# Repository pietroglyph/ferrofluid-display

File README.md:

# ferrofluid-display
Firmware, animation, and control code for a electromagnet-powered ferrofluid display.

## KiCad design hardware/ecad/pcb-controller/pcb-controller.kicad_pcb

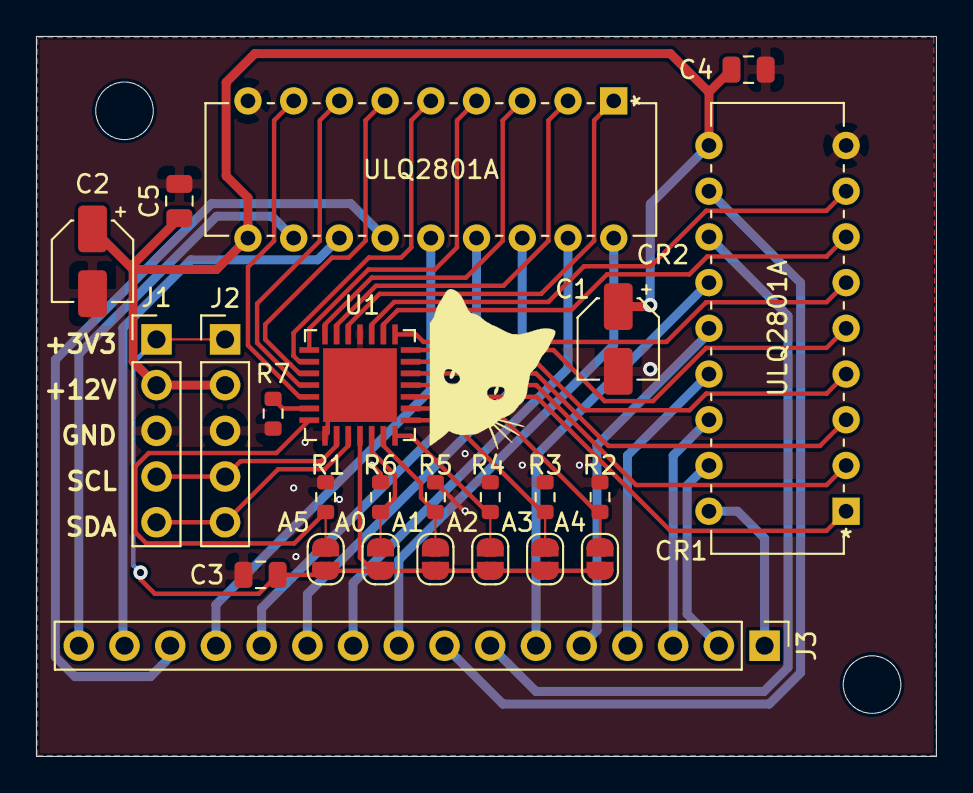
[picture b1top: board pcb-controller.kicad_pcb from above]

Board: 2 copper layers, 50.0 x 40.0 mm, 26 parts (0 on the bottom side), 44 nets.

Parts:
A0, A1, A2, A3, A4, A5: SolderJumper_2_Open; SolderJumper-2_P1.3mm_Open_RoundedPad1.0x1.5mm
C1, C2: CP1; CP_Elec_4x5.4
C3, C4, C5: 0.1 uF; C_0805_2012Metric
CR1, CR2: ULQ2801A
H1, H2: MountingHole; MountingHole_3.2mm_M3
J1, J2: Conn_01x05; PinHeader_1x05_P2.54mm_Vertical
J3: Conn_01x16; PinHeader_1x16_P2.54mm_Vertical
R1, R2, R3, R4, R5, R6, R7: 10k; R_0603_1608Metric
U1: PCA9685BS; QFN65P600X600X100-29N

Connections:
+3V3: A0.1, A1.1, A2.1, A3.1, A4.1, A5.1, C3.1, J1.1, J2.1, U1.25
+12V: C1.1, C2.1, C4.1, C5.1, CR1.10, CR2.10, J1.2, J2.2
/A0: A0.2, R6.1, U1.26
/A1: A1.2, R5.1, U1.27
/A2: A2.2, R4.1, U1.28
/A3: A3.2, R3.1, U1.1
/A4: A4.2, R2.1, U1.2
/A5: A5.2, R1.1, U1.21
GND: C1.2, C2.2, C3.2, C4.2, C5.2, CR1.9, CR2.9, J1.3, J2.3, R1.2, R2.2, R3.2, R4.2, R5.2, R6.2, R7.2, U1.11, U1.22, U1.29
unnamed: CR1.1, U1.3
unnamed: CR1.2, U1.4
unnamed: CR1.3, U1.5
unnamed: CR1.4, U1.6
unnamed: CR1.5, U1.7
unnamed: CR1.6, U1.8
unnamed: CR1.7, U1.9
unnamed: CR1.8, U1.10
unnamed: CR1.11, J3.8
unnamed: CR1.12, J3.7
unnamed: CR1.13, J3.6
unnamed: CR1.14, J3.5
unnamed: CR1.15, J3.4
unnamed: CR1.16, J3.3
unnamed: CR1.17, J3.2
unnamed: CR1.18, J3.1
unnamed: CR2.1, U1.12
unnamed: CR2.2, U1.13
unnamed: CR2.3, U1.14
unnamed: CR2.4, U1.15
unnamed: CR2.5, U1.16
unnamed: CR2.6, U1.17
unnamed: CR2.7, U1.18
unnamed: CR2.8, U1.19
unnamed: CR2.11, J3.16
unnamed: CR2.12, J3.15
unnamed: CR2.13, J3.14
unnamed: CR2.14, J3.13
unnamed: CR2.15, J3.12
unnamed: CR2.16, J3.11
unnamed: CR2.17, J3.10
unnamed: CR2.18, J3.9
unnamed: J1.4, J2.4, U1.23
unnamed: J1.5, J2.5, U1.24
unnamed: R7.1, U1.20

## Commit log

2021-10-31 Update .gitignore to exclude some CMake files
2021-10-31 Add basic project outline
2021-11-04 Set up a compile_commands.json and gitignore for clangd
2021-11-04 Add thresholding- and edge-detection-based display corner detection
2021-11-06 Add hardware directory structure and pcb coil v1
2021-11-06 Add mcad folder
2021-11-07 Add initial work on animation code
2021-11-07 Remove unused options from tracking CMakeLists
2021-11-07 Add initial version of website, with theme and GH action
2021-11-07 deploy: 8cd447ee73312b138034860ab5582cf2dd577925
2021-11-08 Added controller design files. Need to add addresses.
2021-11-08 Added I2C headers and finished PCA9685 schematic wires.
2021-11-08 Fill out website a little bit more
2021-11-08 deploy: efb6bf612e4b9bd919eba291d5f942247d1d5515
2021-11-14 Finished Rev 1 of controller pcb.
2021-11-14 deploy: c7c88280d730185e005096958d3cd155b8f524eb
2021-11-15 Switched to 16 pin header from 32 pin connector. Updated gerber.
2021-11-15 deploy: abc7ec6a708017383b983a7d375b9358067f2693
2021-11-18 Fix visual backend and add test images
2021-11-18 deploy: 252b31852fd4b8733a5ba26198d3494dfbf380dd
2021-11-19 Fixed symbol libraries.
2021-11-24 Added subsystems pages. Put requirements on journey page.
2021-11-24 deploy: 68dbbda1008af753ef7e3fd47abec90abaeec651
2021-12-02 Add simple file backend
2021-12-02 Fix bugs with file backend
2021-12-03 Added Arduino firmware for turning magnets on/off based on coordinate
2021-12-05 Added support for connecting to multiple PCA ICs
2021-12-10 Add better test animation
2021-12-10 Format code and improve handling of different max duty cycles
2021-12-10 Make firmware read from SD and do interpolation and use modern C++
2021-12-10 deploy: c3130c0771fd627b3073a5a7c611cfc3ed057908
2021-12-10 Use correct max duty cycle instead of uint16 maximum
2021-12-10 deploy: 2b08edafac9fc4fc9de33876016798d200687e86
2021-12-11 Added budget.
2021-12-11 Fix serial command parsing and add off command
2021-12-12 Add avr_stl so that we compile for AVR-based Arduinos
2021-12-12 deploy: 1ccc70c4ad434bdfe2e2123518465e2a0fa372df
2021-12-12 Add initial systems page.
2021-12-12 deploy: 3b321c5df0429ae49f3630088eeb76660fbda2ed
2021-12-12 Add shortcodes for page navigation arrows
2021-12-12 Oops forgot to format some animation code
2021-12-12 Pull submodule
2021-12-12 Added content to tank section.
2021-12-12 Create journey page structure
2021-12-12 deploy: a01d33379276a89cc5a79bd3d5627d702e178bca
2021-12-12 Added images to systems.md.
2021-12-12 deploy: eca00d64d520b0ca711811684c26ca2ad0611d8d
2021-12-12 Added Content to Magnets
2021-12-12 deploy: d716388dbbb42d940d0c2795224ccd17d996e76b
2021-12-12 Nuke .gitmodules
2021-12-12 Re-add submodule
2021-12-12 Add serial reading option on mcu and serial writing
2021-12-12 Added Image
2021-12-12 deploy: 4070a99a33f397c962793e3b17ff82bc78767587
2021-12-12 Added SPI sd-card reading for Arduinos
2021-12-13 Add serial backend and serial mode on the MCU
2021-12-13 Add build instructions
2021-12-13 deploy: edf58630346c6725c5c925d4f606dcfe03218655
2021-12-13 deploy: ba1b45fbebad2c7f0c8d01066d3f39bcef6cab83
2021-12-13 deploy: 6b06776d5c89d947905bba1c7b59efa04e472cd2
2021-12-13 deploy: e1718816f56c8bce4979a0c99682d5f80803fbc0
2021-12-13 Added all images
2021-12-13 deploy: cfc870cfd1db609aec2e283486d07da2c406f9d7
2021-12-13 Fixed formatting issue
2021-12-13 Formatting
2021-12-13 deploy: 2f801004fb6e93c99fcbcbf72bde19b2ff8e1d37
2021-12-13 Link to software page
2021-12-13 deploy: 6b574200a85342fe9fd5fe487a53121e22f44d46
2021-12-13 Added content
2021-12-13 deploy: c32101705336ac743b6af1ff2e3d765380d01aac
2021-12-13 typo fix
2021-12-13 deploy: d66add1095ca6da0575e9127a45a89392f23972b
2021-12-13 Updated bits about the magnets
2021-12-13 deploy: f23780b4299f2377c2fa2c1cad0dbae400d21977
2021-12-13 Formatting Fix
2021-12-13 deploy: 15d3bf9ed4991c088ef869109ffb3d26e8d24838
2021-12-14 Added images to systems. Removed unused markdown documents.
2021-12-14 deploy: f077ff59d7db6f8de2ff280f03fb506d1cb02c9f
2021-12-14 Add libfmt archive file
    Shouldn't need to do this but CMake insists and I don't have time to fix
    it right now.
2021-12-14 Add MathJax support and set dates correctly
2021-12-14 deploy: c380f5dd85a07b816ee0c70a5c7e9d5eb4e77b64
2021-12-14 Fixed an image
2021-12-14 deploy: fae40614696febd07529154357d10a817406268d
2021-12-14 Mathjax test
2021-12-14 deploy: ea3aded78e3edb5619d95f2b4eb5ede83182715b
2021-12-14 Added new ferrofluid gif. Added about section for team bios.
2021-12-14 deploy: 2dc65e0f66b384acd8dae2c737a70fc95a444031
2021-12-14 Updated todo list.
2021-12-14 deploy: 484aae5dac59ec82b17e3316da0642f84e8be158
2021-12-14 Add software writeup
2021-12-14 deploy: f583565dd1a840560fd0bff6b0351d84065f2401
2021-12-14 Arduino firmware now attempts to open files by default, open first file as a fallback
2021-12-14 Added images
2021-12-14 deploy: 6752fd347a42c1b2712869ecc5bfbba0a2037f8b
2021-12-14 Added Sprint One Content
2021-12-14 deploy: 8c25b15fd9d74fcdfe90cdcb0da9fe54db8e086d
2021-12-14 deploy: 32baa48a1dae1ee465ba83a17082f7d7b073a6de
2021-12-14 deploy: 7cb77552cd864e16a42be73d8056da395b0d8fad
2021-12-14 Added arrows to access nav bar. Fixed broken image links.
2021-12-14 deploy: 71e88d5a58b8e7f469e61f1ec698e93192613c17
2021-12-14 Fix heading format and typos
2021-12-14 Fill in Sprint 3 content
2021-12-14 deploy: 2f56c21f394058bfd27d8ee2dbb22c82ed6ee1e8
2021-12-14 Fixed image paths
2021-12-14 deploy: 7ab910c89722efa4a78ead95718759ac19a2ac99
2021-12-14 Added Demo Day Section
2021-12-14 deploy: 95b5b63cf42db26c5c7ee7351b29e115b5663901
2021-12-14 deploy: 544f3837ceff39d7bb39564fac6f003f01a615dd
2021-12-14 Added video of working tank
2021-12-14 deploy: 64ec418ad2d2e1fbfb65cf65cd7c6a51d74b41b1
2021-12-14 Added Info to Demo Day
2021-12-14 deploy: 95238d4c6df194c6ee9d909439417a3a8542b490
2021-12-14 deploy: 75f4771ceed83362183c467b175844304e2c3058
2021-12-14 Added tank information in Journey and Sprint 2 information
2021-12-14 Added the ability to change frametime via serial command
2021-12-14 deploy: e8c1cd945044d0efa178cd2c7ffd7d14ce126a69
2021-12-14 Edited systems page. Changes call to action button to systems.
2021-12-14 deploy: b023a0b13dc833d266f6cea03c34a25165831286
2021-12-14 Added more images to front page
2021-12-14 deploy: 4347411cc839659ca13642f0b3a5981d68884a01
2021-12-14 Remove unneeded parts of footer
2021-12-14 Add about page and make it look alright
2021-12-14 Add a little more info to the journey section
2021-12-14 Add headshots that were accidentally left uncomitted
2021-12-14 deploy: c530540b3541653d396e5287441b895a6e5518bf

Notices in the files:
parts and their libraries:
Copyright 2021 Accelerated Designs. All rights reserved.
